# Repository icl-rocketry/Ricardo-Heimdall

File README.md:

Need to add v monitoring to include the buck stuff from chad
Need to add 6v led to know when servo voltage is on

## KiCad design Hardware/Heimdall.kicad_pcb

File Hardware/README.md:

# Ricardo Board Template
This is a KiCad template including the required components for an ESP32S3 with a USB-C port, a CAN transceiver, as well as logic power input regulation. This is the bare minimum needed for boards in the ricardo ecosystem. If you have followed the [hardware library usage instructions](https://github.com/icl-rocketry/iclr-hw), the hardware libraries will automatically be added to every project started from this template.

## Usage
To use this, clone this repository in your KiCad user templates folder.

By default, this folder is:

MacOS - ```/Users/{USERNAME}/Documents/KiCad/8.0/template/```

Windows -  ```%USERPROFILE%/Documents/KiCad/8.0/template```

Linux - ```/home/{USERNAME}/.local/share/kicad/8.0/template```

Then, you will be able to access the template when making a new project in ```KiCad -> File -> New Project from Template... -> User Templates```

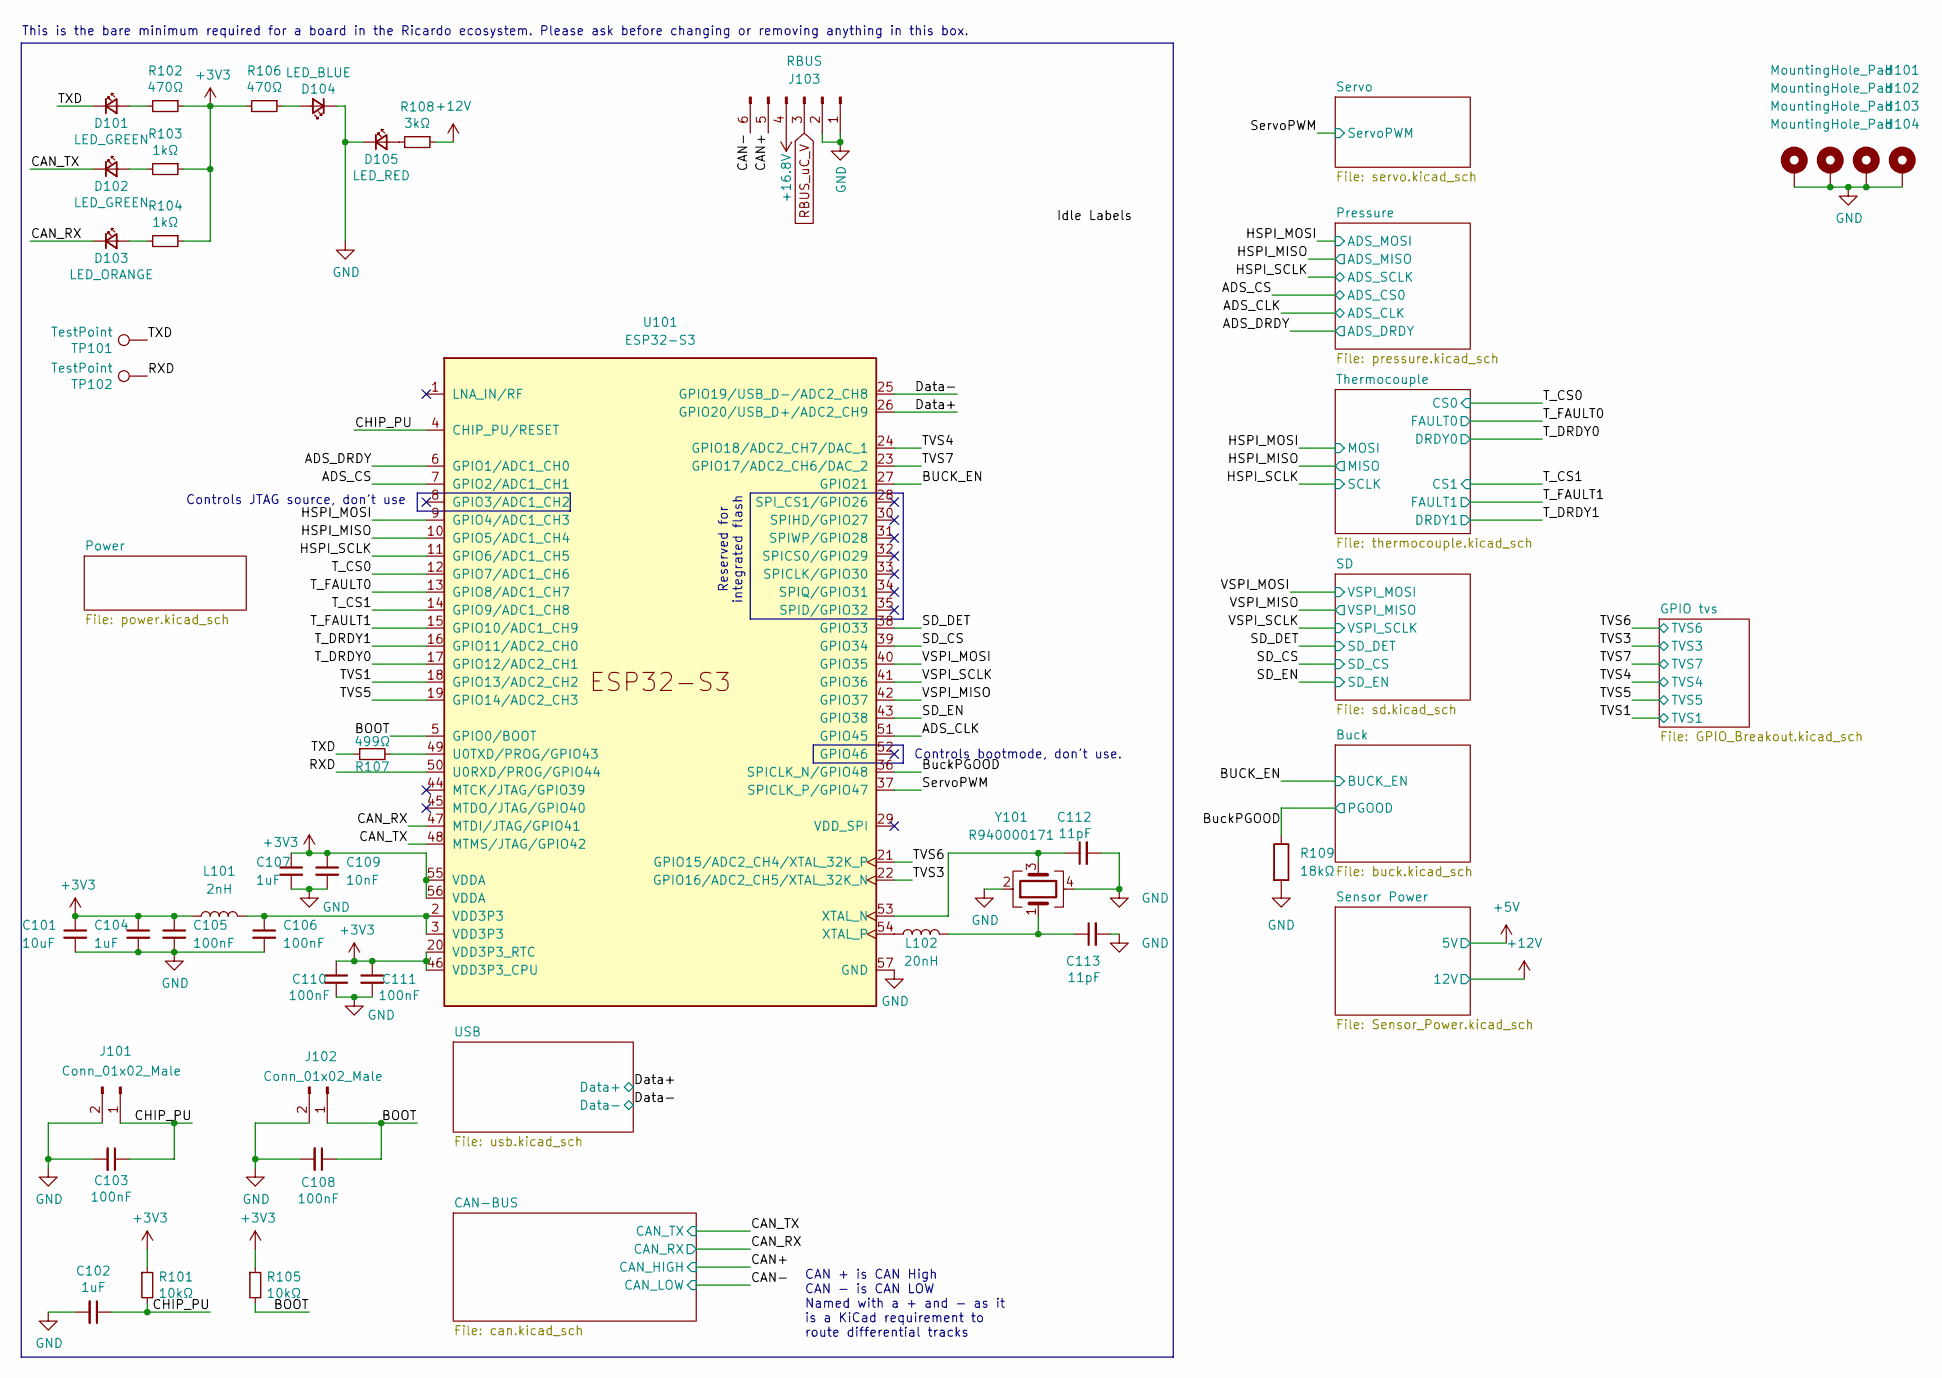
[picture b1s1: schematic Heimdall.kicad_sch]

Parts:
C101: 10uF; C_0402_1005Metric
C102, C104, C107: 1uF; C_0402_1005Metric
C103, C105, C106, C108, C110, C111: 100nF; C_0402_1005Metric
C109: 10nF; C_0402_1005Metric
C112, C113: 11pF; C_0402_1005Metric
D101, D102: LED_GREEN; LED_0402_1005Metric
D103: LED_ORANGE; LED_0402_1005Metric
D104: LED_BLUE; LED_0402_1005Metric
D105: LED_RED; LED_0402_1005Metric
H101, H102, H103, H104: MountingHole_Pad; MountingHole_3.2mm_M3_DIN965_Pad
J101, J102: Conn_01x02_Male; PinHeader_1x02_P2.54mm_Vertical
J103: RBUS; Molex_Mini-Fit_Jr_5569-06A2_2x03_P4.20mm_Horizontal
L101: 2nH; L_0402_1005Metric
L102: 20nH; L_0402_1005Metric
R101, R105: 10kΩ; R_0402_1005Metric
R102, R106: 470Ω; R_0402_1005Metric
R103, R104: 1kΩ; R_0402_1005Metric
R107: 499Ω; R_0402_1005Metric
R108: 3kΩ; R_0402_1005Metric
R109: 18kΩ; R_0402_1005Metric
TP101, TP102: TestPoint; TestPoint_Pad_D1.0mm
U101: ESP32-S3; QFN40P700X700X90-57N
Y101: R940000171; Crystal_SMD_2016-4Pin_2.0x1.6mm

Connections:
+3V3: C101.1, C104.1, C105.1, C107.1, C109.1, C110.1, C111.1, L101.1, R101.1, R102.1, R103.1, R104.1, R105.1, R106.2, U101.20 (VDD3P3_RTC), U101.46 (VDD3P3_CPU), U101.55 (VDDA), U101.56 (VDDA); also elsewhere on the board
+12V: R108.1; also elsewhere on the board
+16.8V: J103.4; also elsewhere on the board
/ADS_CLK: U101.51 (GPIO45); also elsewhere on the board
/ADS_CS: U101.7 (GPIO2/ADC1_CH1); also elsewhere on the board
/ADS_DRDY: U101.6 (GPIO1/ADC1_CH0); also elsewhere on the board
/BOOT: C108.1, J102.1, R105.2, U101.5 (GPIO0/BOOT)
/BUCK_EN: U101.27 (GPIO21); also elsewhere on the board
/BuckPGOOD: R109.1, U101.36 (SPICLK_N/GPIO48); also elsewhere on the board
/CAN+: J103.5; also elsewhere on the board
/CAN-: J103.6; also elsewhere on the board
/CAN_RX: D103.1 (K), U101.47 (MTDI/JTAG/GPIO41); also elsewhere on the board
/CAN_TX: D102.1 (K), U101.48 (MTMS/JTAG/GPIO42); also elsewhere on the board
/CHIP_PU: C102.1, C103.1, J101.1, R101.2, U101.4 (CHIP_PU/RESET)
/Data+: U101.26 (GPIO20/USB_D+/ADC2_CH9); also elsewhere on the board
/Data-: U101.25 (GPIO19/USB_D-/ADC2_CH8); also elsewhere on the board
/HSPI_MISO: U101.10 (GPIO5/ADC1_CH4); also elsewhere on the board
/HSPI_MOSI: U101.9 (GPIO4/ADC1_CH3); also elsewhere on the board
/HSPI_SCLK: U101.11 (GPIO6/ADC1_CH5); also elsewhere on the board
/RXD: TP102.1, U101.50 (U0RXD/PROG/GPIO44)
/SD_CS: U101.39 (GPIO34); also elsewhere on the board
/SD_DET: U101.38 (GPIO33); also elsewhere on the board
/SD_EN: U101.43 (GPIO38); also elsewhere on the board
/ServoPWM: U101.37 (SPICLK_P/GPIO47); also elsewhere on the board
/TVS1: U101.18 (GPIO13/ADC2_CH2); also elsewhere on the board
/TVS3: U101.22 (GPIO16/ADC2_CH5/XTAL_32K_N); also elsewhere on the board
/TVS4: U101.24 (GPIO18/ADC2_CH7/DAC_1); also elsewhere on the board
/TVS5: U101.19 (GPIO14/ADC2_CH3); also elsewhere on the board
/TVS6: U101.21 (GPIO15/ADC2_CH4/XTAL_32K_P); also elsewhere on the board
/TVS7: U101.23 (GPIO17/ADC2_CH6/DAC_2); also elsewhere on the board
/TXD: D101.1 (K), R107.1, TP101.1
/T_CS0: U101.12 (GPIO7/ADC1_CH6); also elsewhere on the board
/T_CS1: U101.14 (GPIO9/ADC1_CH8); also elsewhere on the board
/T_DRDY0: U101.17 (GPIO12/ADC2_CH1); also elsewhere on the board
/T_DRDY1: U101.16 (GPIO11/ADC2_CH0); also elsewhere on the board
/T_FAULT0: U101.13 (GPIO8/ADC1_CH7); also elsewhere on the board
/T_FAULT1: U101.15 (GPIO10/ADC1_CH9); also elsewhere on the board
/VSPI_MISO: U101.42 (GPIO37); also elsewhere on the board
/VSPI_MOSI: U101.40 (GPIO35); also elsewhere on the board
/VSPI_SCLK: U101.41 (GPIO36); also elsewhere on the board
GND: C101.2, C102.2, C103.2, C104.2, C105.2, C106.2, C107.2, C108.2, C109.2, C110.2, C111.2, C112.2, C113.2, D104.1 (K), D105.1 (K), H101.1, H102.1, H103.1, H104.1, J101.2, J102.2, J103.1, J103.2, R109.2, U101.57 (GND), Y101.2, Y101.4; also elsewhere on the board
unnamed: C106.1, L101.2, U101.2 (VDD3P3), U101.3 (VDD3P3)
unnamed: C113.1, L102.2, Y101.1
unnamed: D101.2 (A), R102.2
unnamed: D102.2 (A), R103.2
unnamed: D103.2 (A), R104.2
unnamed: D104.2 (A), R106.1
unnamed: D105.2 (A), R108.2
unnamed: R107.2, U101.49 (U0TXD/PROG/GPIO43)
unnamed: C112.1, U101.53 (XTAL_N), Y101.3
unnamed: L102.1, U101.54 (XTAL_P)
RBUS_uC_V: J103.3; also elsewhere on the board

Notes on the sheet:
Controls bootmode, don't use.
This is the bare minimum required for a board in the Ricardo ecosystem. Please ask before changing or removing anything in this box.
CAN + is CAN High CAN - is CAN LOW Named with a + and - as it is a KiCad requirement to route differential tracks
Controls JTAG source, don't use
Reserved for integrated flash

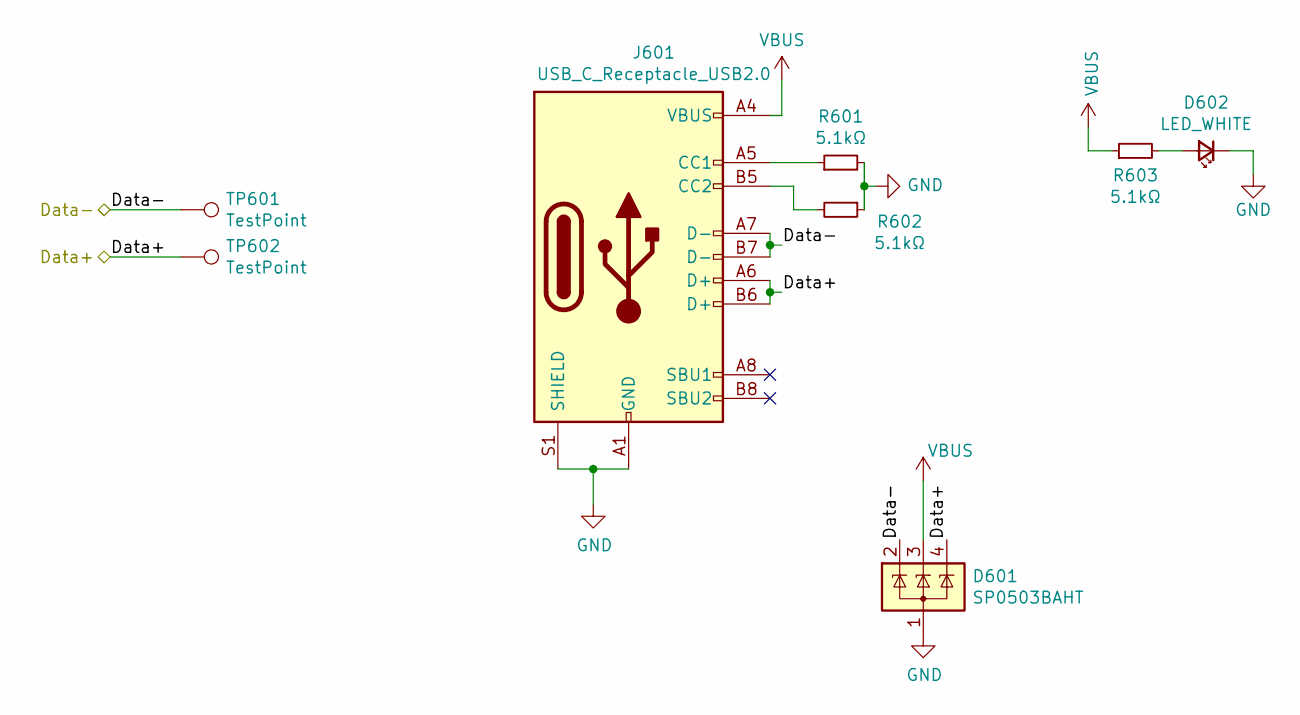
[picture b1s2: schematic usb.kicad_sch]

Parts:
D601: SP0503BAHT; SOT-143
D602: LED_WHITE; LED_0402_1005Metric
J601: USB_C_Receptacle_USB2.0; USB_C_Receptacle_Palconn_UTC16-G
R601, R602, R603: 5.1kΩ; R_0402_1005Metric
TP601, TP602: TestPoint; TestPoint_Pad_D1.0mm

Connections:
/Data+: D601.4 (K), J601.A6 (D+), J601.B6 (D+), TP602.1; also elsewhere on the board
/Data-: D601.2 (K), J601.A7 (D-), J601.B7 (D-), TP601.1; also elsewhere on the board
GND: D601.1 (A), D602.1 (K), J601.A1 (GND), J601.A12 (GND), J601.B1 (GND), J601.B12 (GND), J601.S1 (SHIELD), R601.2, R602.1; also elsewhere on the board
unnamed: D602.2 (A), R603.2
unnamed: J601.A5 (CC1), R601.1
unnamed: J601.B5 (CC2), R602.2
VBUS: D601.3 (K), J601.A4 (VBUS), J601.A9 (VBUS), J601.B4 (VBUS), J601.B9 (VBUS), R603.1; also elsewhere on the board

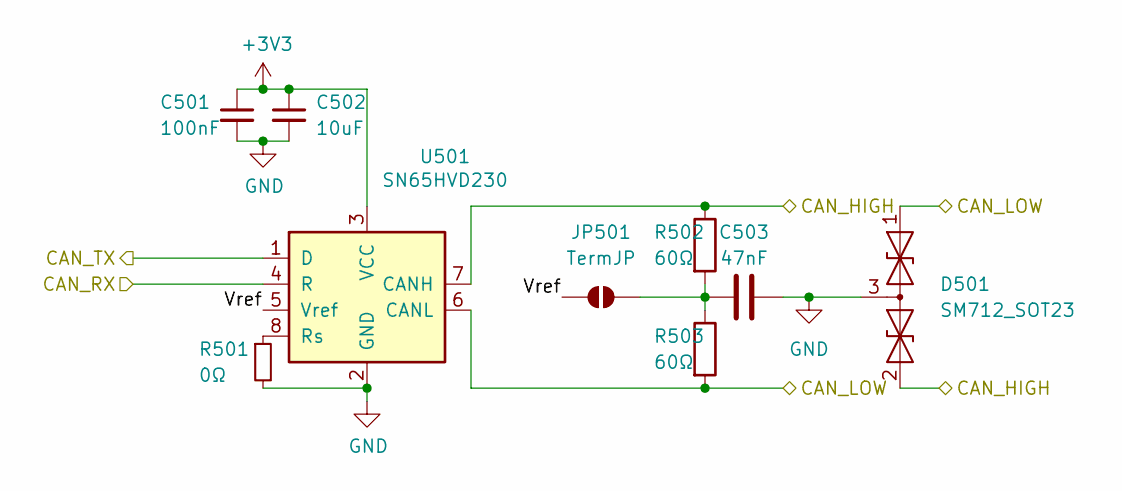
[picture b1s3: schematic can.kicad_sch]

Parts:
C501: 100nF; C_0402_1005Metric
C502: 10uF; C_0402_1005Metric
C503: 47nF; C_0402_1005Metric
D501: SM712_SOT23; SOT-23
JP501: TermJP; SmallerSolderJP
R501: 0Ω; R_0402_1005Metric
R502, R503: 60Ω; R_0603_1608Metric
U501: SN65HVD230; SOIC-8_3.9x4.9mm_P1.27mm

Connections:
+3V3: C501.1, C502.1, U501.3 (VCC); also elsewhere on the board
/CAN+: D501.2 (A2), R502.1, U501.7 (CANH); also elsewhere on the board
/CAN-: D501.1 (A1), R503.2, U501.6 (CANL); also elsewhere on the board
/CAN-BUS/Vref: JP501.1 (A), U501.5 (Vref)
/CAN_RX: U501.4 (R); also elsewhere on the board
/CAN_TX: U501.1 (D); also elsewhere on the board
GND: C501.2, C502.2, C503.2, D501.3 (common), R501.2, U501.2 (GND); also elsewhere on the board
unnamed: C503.1, JP501.2 (B), R502.2, R503.1
unnamed: R501.1, U501.8 (Rs)

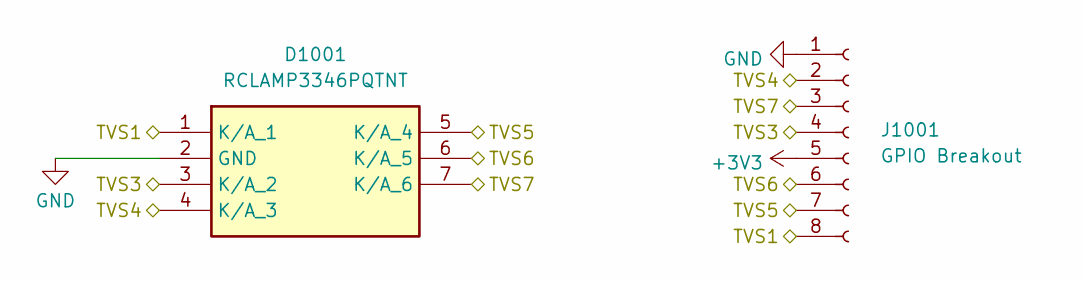
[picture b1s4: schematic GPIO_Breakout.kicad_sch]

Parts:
D1001: RCLAMP3346PQTNT; Mouser Part Number 947-RCLAMP3346PQTNT
J1001: GPIO Breakout; PinSocket_2x04_P2.54mm_Vertical

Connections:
+3V3: J1001.5; also elsewhere on the board
/TVS1: D1001.1 (K/A_1), J1001.8; also elsewhere on the board
/TVS3: D1001.3 (K/A_2), J1001.4; also elsewhere on the board
/TVS4: D1001.4 (K/A_3), J1001.2; also elsewhere on the board
/TVS5: D1001.5 (K/A_4), J1001.7; also elsewhere on the board
/TVS6: D1001.6 (K/A_5), J1001.6; also elsewhere on the board
/TVS7: D1001.7 (K/A_6), J1001.3; also elsewhere on the board
GND: D1001.2 (GND), J1001.1; also elsewhere on the board

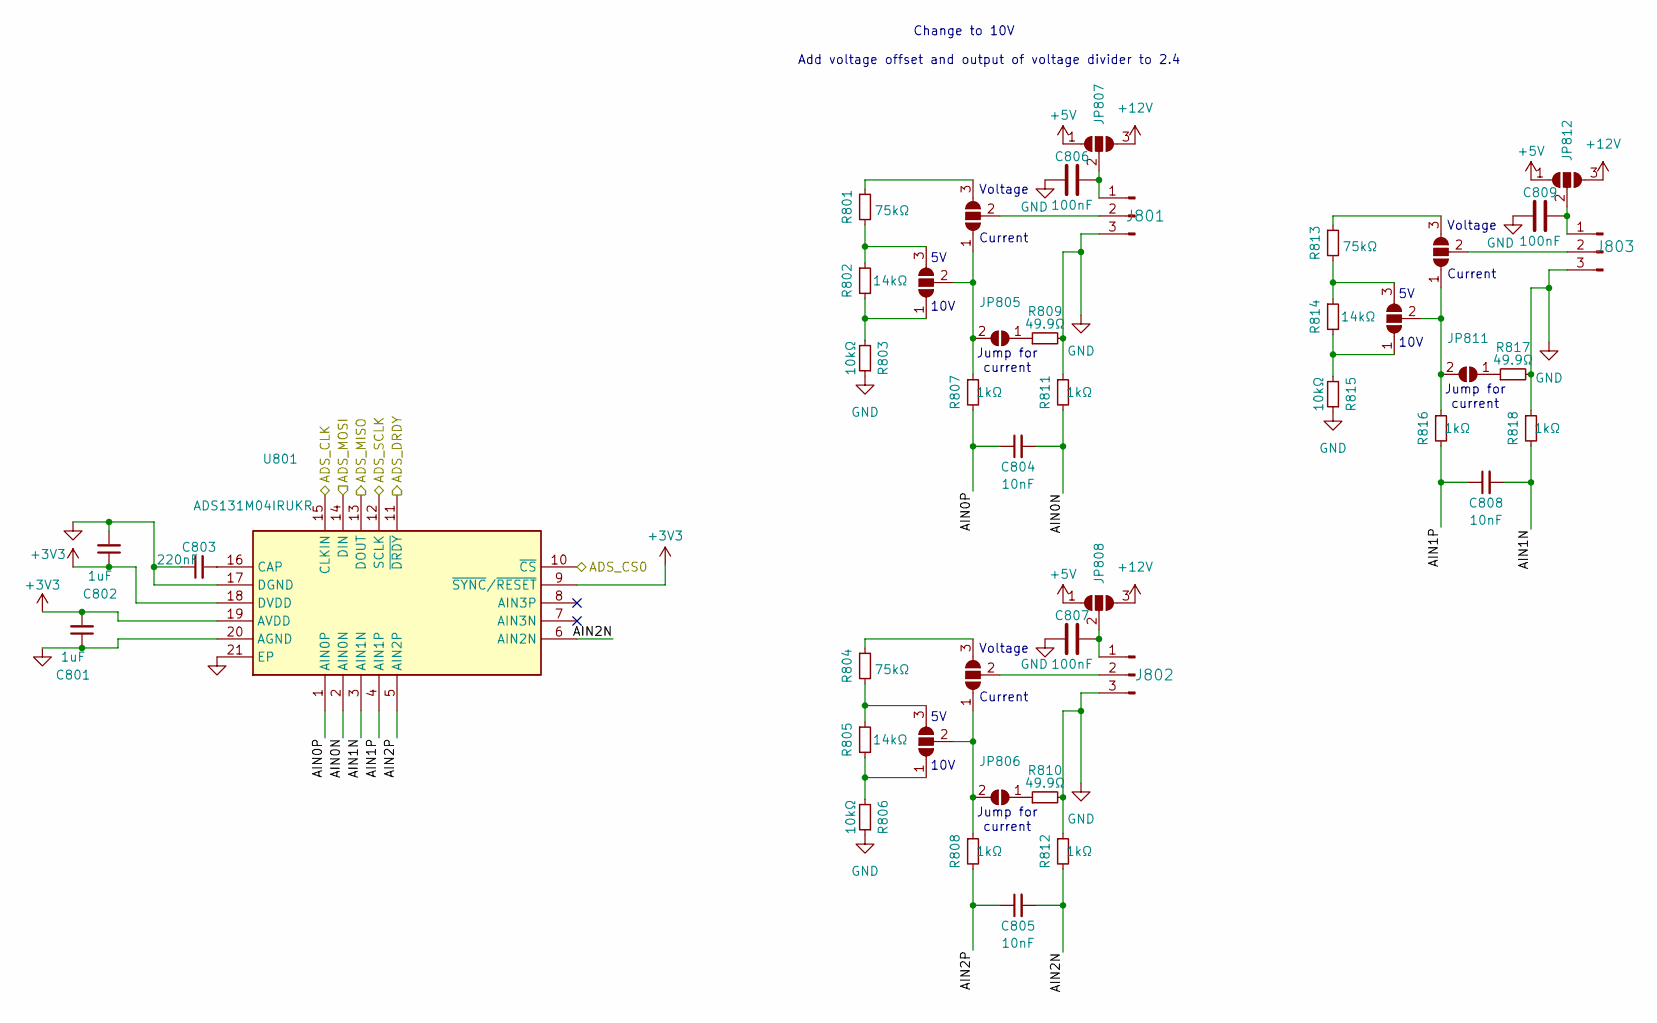
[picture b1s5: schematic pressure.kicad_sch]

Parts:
C801, C802: 1uF; C_0402_1005Metric
C803: 220nF; C_0402_1005Metric
C804, C805, C808: 10nF; C_0402_1005Metric
C806, C807, C809: 100nF; C_0402_1005Metric
J801, J802, J803: 1053131103; Molex_Nano-Fit_105313-xx03_1x03_P2.50mm_Horizontal
JP801, JP802, JP803, JP804, JP807, JP808, JP809, JP810, JP812: SolderJumper_3_Open; SolderJumper-3_P1.3mm_Open_RoundedPad1.0x1.5mm_NumberLabels
JP805, JP806, JP811: SolderJumper_2_Open; SmallerSolderJP
R801, R804, R813: 75kΩ; R_0402_1005Metric; MPN RT0402BRD0775KL
R802, R805, R814: 14kΩ; R_0402_1005Metric; MPN 0402WGF1402TCE
R803, R806, R815: 10kΩ; R_0402_1005Metric; MPN ERA2ARB103X
R807, R808, R811, R812, R816, R818: 1kΩ; R_0402_1005Metric
R809, R810, R817: 49.9Ω; R_0402_1005Metric; MPN RT0402BRD0749R9L
U801: ADS131M04IRUKR; QFN40P300X300X80-21N-D; Manufacturer_Part_Number ADS131M04IRUKR; Mouser Part Number 595-ADS131M04IRUKR

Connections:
+3V3: C801.2, C802.1, U801.9 (~SYNC/~RESET), U801.18 (DVDD), U801.19 (AVDD); also elsewhere on the board
+5V: JP807.1 (A), JP808.1 (A), JP812.1 (A); also elsewhere on the board
+12V: JP807.3 (B), JP808.3 (B), JP812.3 (B); also elsewhere on the board
/ADS_CLK: U801.15 (CLKIN); also elsewhere on the board
/ADS_CS: U801.10 (~CS); also elsewhere on the board
/ADS_DRDY: U801.11 (~DRDY); also elsewhere on the board
/HSPI_MISO: U801.13 (DOUT); also elsewhere on the board
/HSPI_MOSI: U801.14 (DIN); also elsewhere on the board
/HSPI_SCLK: U801.12 (SCLK); also elsewhere on the board
/Pressure/AIN0N: C804.2, R811.2, U801.2 (AIN0N)
/Pressure/AIN0P: C804.1, R807.2, U801.1 (AIN0P)
/Pressure/AIN1N: C808.2, R818.2, U801.3 (AIN1N)
/Pressure/AIN1P: C808.1, R816.2, U801.4 (AIN1P)
/Pressure/AIN2N: C805.2, R812.2, U801.6 (AIN2N)
/Pressure/AIN2P: C805.1, R808.2, U801.5 (AIN2P)
GND: C801.1, C802.2, C803.1, C806.1, C807.1, C809.1, J801.3, J802.3, J803.3, R803.1, R806.1, R809.2, R810.2, R811.1, R812.1, R815.1, R817.2, R818.1, U801.17 (DGND), U801.20 (AGND), U801.21 (EP); also elsewhere on the board
unnamed: C806.2, J801.1, JP807.2 (C)
unnamed: J801.2, JP803.2 (C)
unnamed: C807.2, J802.1, JP808.2 (C)
unnamed: J802.2, JP804.2 (C)
unnamed: C809.2, J803.1, JP812.2 (C)
unnamed: J803.2, JP810.2 (C)
unnamed: JP801.1 (A), R802.2, R803.2
unnamed: JP801.3 (B), R801.2, R802.1
unnamed: JP801.2 (C), JP803.1 (A), JP805.2 (B), R807.1
unnamed: JP802.1 (A), R805.2, R806.2
unnamed: JP802.3 (B), R804.2, R805.1
unnamed: JP802.2 (C), JP804.1 (A), JP806.2 (B), R808.1
unnamed: JP803.3 (B), R801.1
unnamed: JP804.3 (B), R804.1
unnamed: JP805.1 (A), R809.1
unnamed: JP806.1 (A), R810.1
unnamed: JP809.1 (A), R814.2, R815.2
unnamed: JP809.3 (B), R813.2, R814.1
unnamed: JP809.2 (C), JP810.1 (A), JP811.2 (B), R816.1
unnamed: JP810.3 (B), R813.1
unnamed: JP811.1 (A), R817.1
unnamed: C803.2, U801.16 (CAP)

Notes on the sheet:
Jump for current
10V
Add voltage offset and output of voltage divider to 2.4
Voltage
Change to 10V
Current

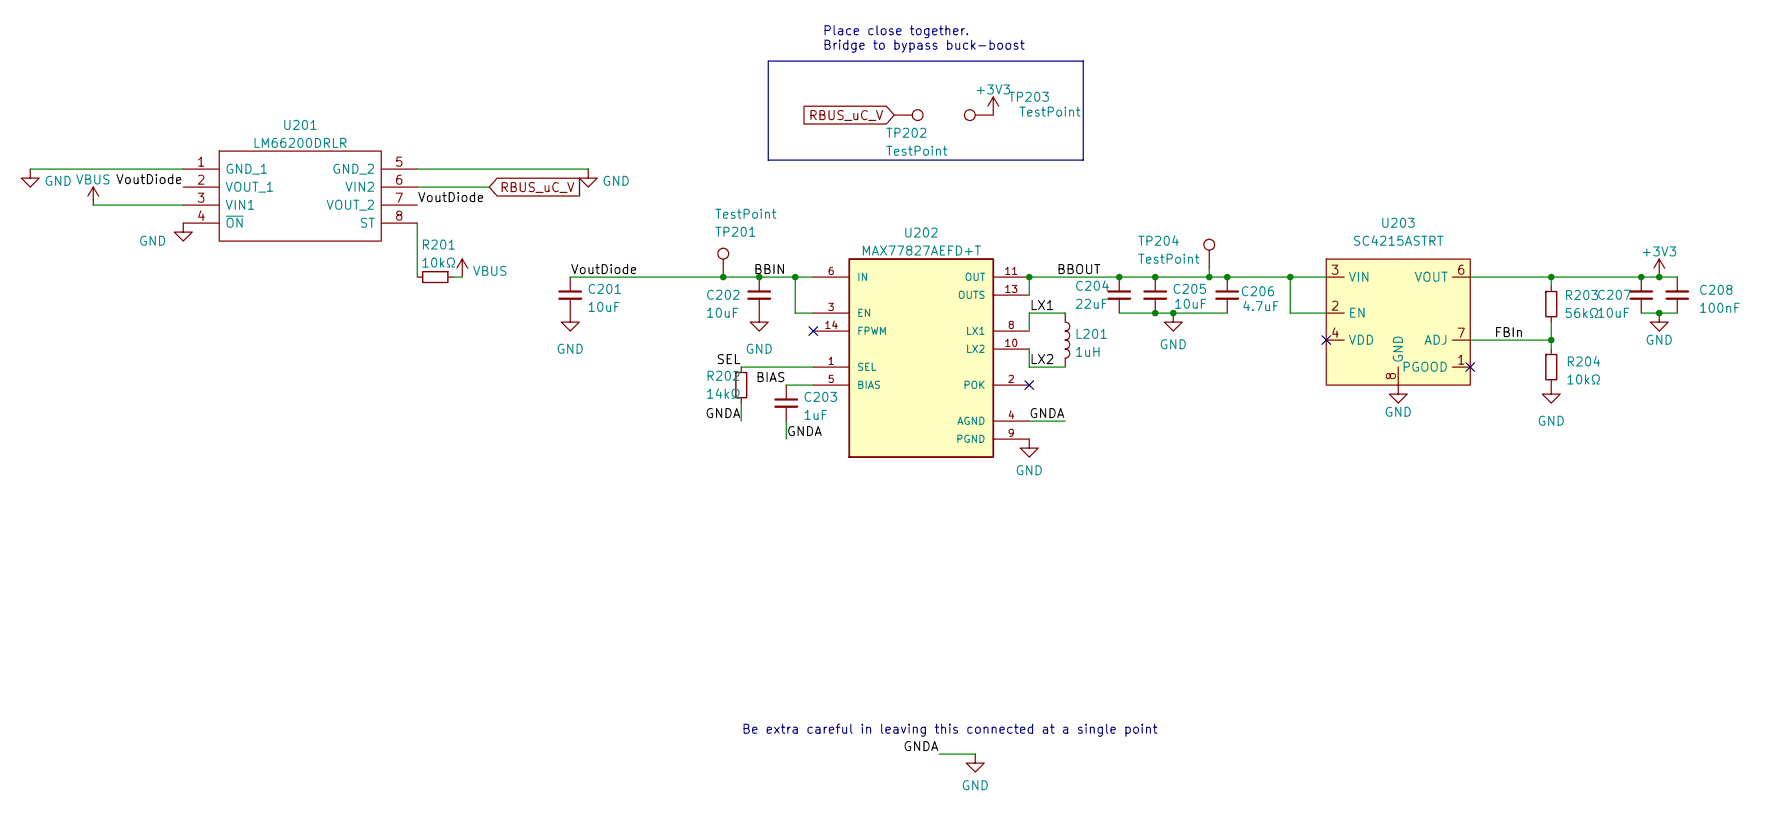
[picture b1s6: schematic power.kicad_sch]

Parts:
C201, C205, C207: 10uF; C_0402_1005Metric
C202: 10uF; C_0603_1608Metric
C203: 1uF; C_0402_1005Metric
C204: 22uF; C_0603_1608Metric
C206: 4.7uF; C_0402_1005Metric
C208: 100nF; C_0402_1005Metric
L201: 1uH; L_0805_2012Metric
R201, R204: 10kΩ; R_0402_1005Metric
R202: 14kΩ; R_0402_1005Metric
R203: 56kΩ; R_0402_1005Metric
TP201, TP202, TP203, TP204: TestPoint; TestPoint_Pad_D1.5mm
U201: LM66200DRLR; SOTFL50P160X60-8N; Manufacturer_Part_Number LM66200DRLR; Mouser Part Number 595-LM66200DRLR
U202: MAX77827AEFD+T; CONV_MAX77827AEFD+T; PARTREV B
U203: SC4215ASTRT; SOIC127P599X175-9N

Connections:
+3V3: C207.2, C208.2, R203.1, TP203.1, U203.6 (VOUT); also elsewhere on the board
/Power/BBIN: C201.1, C202.1, TP201.1, U201.2 (VOUT_1), U201.7 (VOUT_2), U202.3 (EN), U202.6 (IN)
/Power/BBOUT: C204.1, C205.1, C206.1, TP204.1, U202.11 (OUT), U202.13 (OUTS), U203.2 (EN), U203.3 (VIN)
/Power/BIAS: C203.1, U202.5 (BIAS)
/Power/FBIn: R203.2, R204.1, U203.7 (ADJ)
/Power/LX1: L201.1, U202.8 (LX1)
/Power/LX2: L201.2, U202.10 (LX2)
/Power/SEL: R202.1, U202.1 (SEL)
GND: C201.2, C202.2, C203.2, C204.2, C205.2, C206.2, C207.1, C208.1, R202.2, R204.2, U201.1 (GND_1), U201.4 (~ON), U201.5 (GND_2), U202.4 (AGND), U202.9 (PGND), U203.8 (GND), U203.9 (GND); also elsewhere on the board
unnamed: R201.2, U201.8 (ST)
RBUS_uC_V: TP202.1, U201.6 (VIN2); also elsewhere on the board
VBUS: R201.1, U201.3 (VIN1); also elsewhere on the board

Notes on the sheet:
Place close together. Bridge to bypass buck-boost
Be extra careful in leaving this connected at a single point

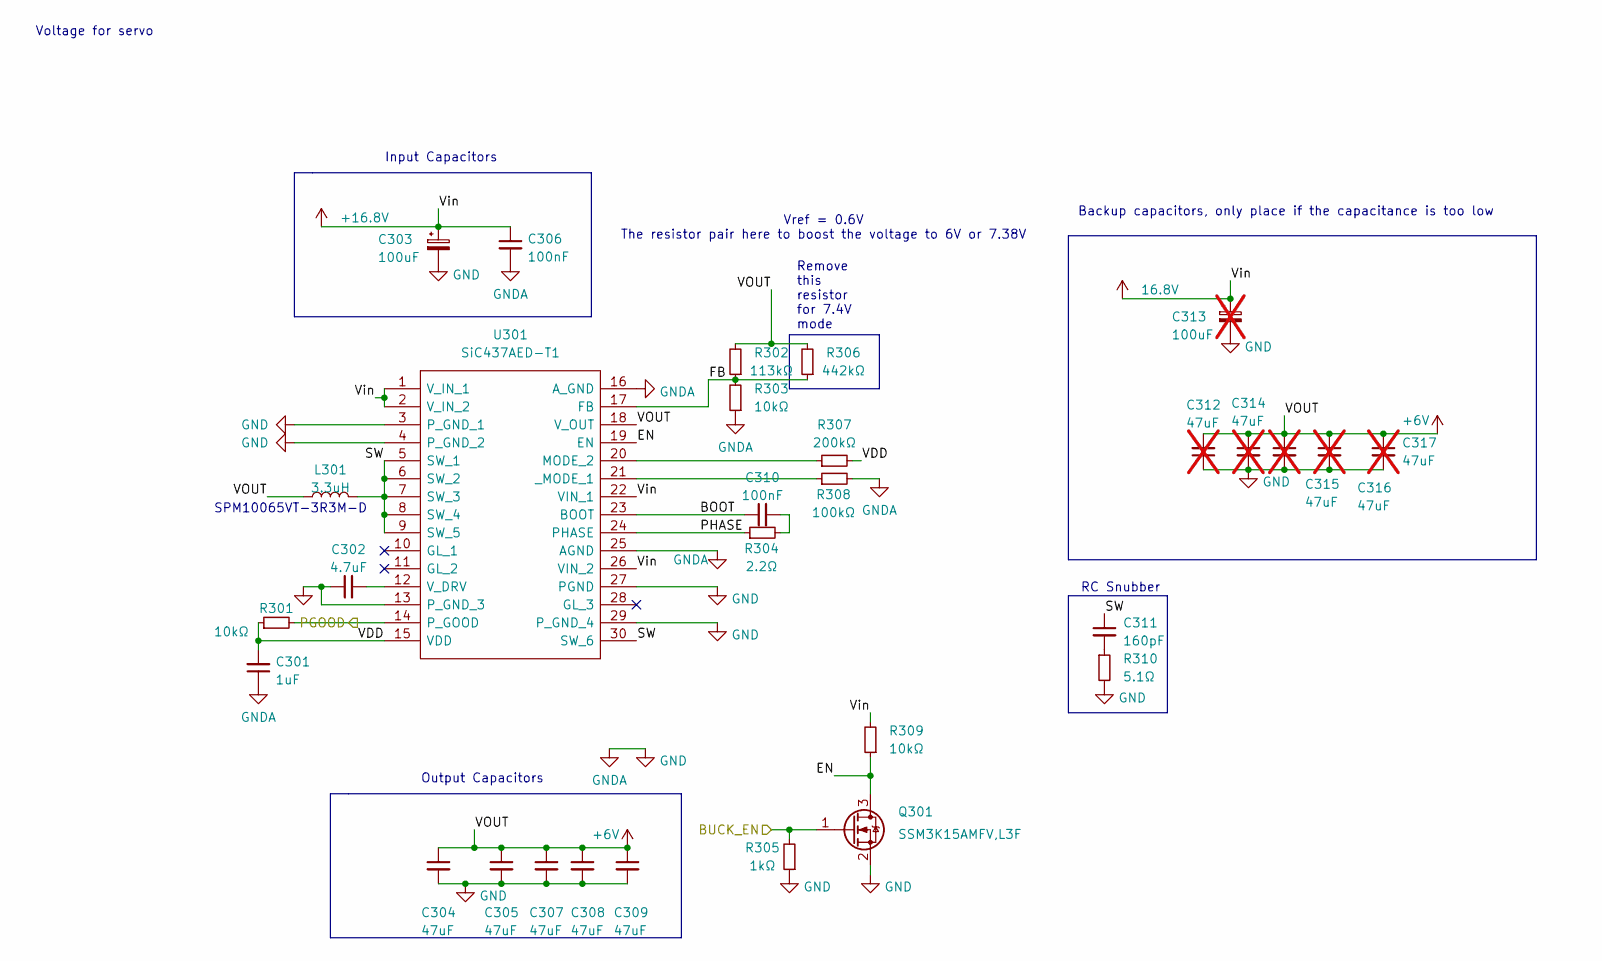
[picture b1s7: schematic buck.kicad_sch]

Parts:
C301: 1uF; C_0402_1005Metric
C302: 4.7uF; C_0402_1005Metric
C303: 100uF; CP_EIA-7360-38_Kemet-E; MPN T52M1107M035C0100
C304, C305, C307, C308, C309: 47uF; C_1206_3216Metric
C306, C310: 100nF; C_0402_1005Metric
C311: 160pF; C_0603_1608Metric
C312, C314, C315, C316, C317: 47uF; C_1206_3216Metric; not fitted
C313: 100uF; CP_EIA-7360-38_Kemet-E; MPN T52M1107M035C0100; not fitted
L301: 3.3uH; IND_SPM10065VT-3R3M-D; MPN SPM10065VT-3R3M-D
Q301: SSM3K15AMFV,L3F; SOT-723
R301, R303, R309: 10kΩ; R_0402_1005Metric
R302: 113kΩ; R_0402_1005Metric; MPN ERJ-2RKF1133X
R304: 2.2Ω; R_0402_1005Metric
R305: 1kΩ; R_0402_1005Metric
R306: 442kΩ; R_0402_1005Metric; MPN ERJ-2RKF4423X
R307: 200kΩ; R_0402_1005Metric
R308: 100kΩ; R_0402_1005Metric
R310: 5.1Ω; R_0603_1608Metric
U301: SiC437AED-T1; SiC437BEDT1GE3; Manufacturer_Part_Number SiC437BED-T1-GE3; Mouser Part Number 78-SIC437BED-T1-GE3

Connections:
+6V: C304.1, C305.1, C307.1, C308.1, C309.1, C312.2, C314.1, C315.1, C316.1, C317.1, L301.1, R302.2, R306.2, U301.18 (V_OUT); also elsewhere on the board
+16.8V: C303.1, C306.1, C313.1, R309.2, U301.1 (V_IN_1), U301.2 (V_IN_2), U301.22 (VIN_1), U301.26 (VIN_2); also elsewhere on the board
/BUCK_EN: Q301.1 (G), R305.2; also elsewhere on the board
/Buck/BOOT: C310.1, U301.23 (BOOT)
/Buck/EN: Q301.3 (D), R309.1, U301.19 (EN)
/Buck/FB: R302.1, R303.2, R306.1, U301.17 (FB)
/Buck/PHASE: R304.1, U301.24 (PHASE)
/Buck/SW: C311.1, L301.2, U301.5 (SW_1), U301.6 (SW_2), U301.7 (SW_3), U301.8 (SW_4), U301.9 (SW_5), U301.30 (SW_6)
/Buck/VDD: C301.2, R301.1, R307.2, U301.15 (VDD)
/BuckPGOOD: R301.2, U301.14 (P_GOOD); also elsewhere on the board
GND: C301.1, C302.1, C303.2, C304.2, C305.2, C306.2, C307.2, C308.2, C309.2, C312.1, C313.2, C314.2, C315.2, C316.2, C317.2, Q301.2 (S), R303.1, R305.1, R308.2, R310.2, U301.3 (P_GND_1), U301.4 (P_GND_2), U301.13 (P_GND_3), U301.16 (A_GND), U301.25 (AGND), U301.27 (PGND), U301.29 (P_GND_4); also elsewhere on the board
unnamed: C310.2, R304.2
unnamed: C311.2, R310.1
unnamed: R307.1, U301.20 (MODE_2)
unnamed: C302.2, U301.12 (V_DRV)
unnamed: R308.1, U301.21 (_MODE_1)

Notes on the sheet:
SPM10065VT-3R3M-D
Voltage for servo
Output Capacitors
Backup capacitors, only place if the capacitance is too low
Input Capacitors
Vref = 0.6V The resistor pair here to boost the voltage to 6V or 7.38V
RC Snubber
Remove this resistor for 7.4V mode

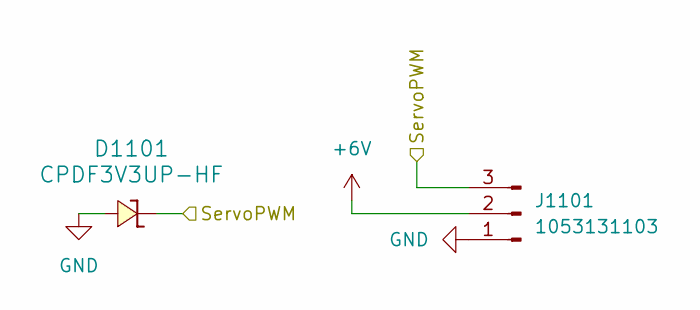
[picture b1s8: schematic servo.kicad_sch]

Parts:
D1101: CPDF3V3UP-HF; CPD
J1101: 1053131103; Molex_Nano-Fit_105313-xx03_1x03_P2.50mm_Horizontal

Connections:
+6V: J1101.2; also elsewhere on the board
/ServoPWM: D1101.2, J1101.3; also elsewhere on the board
GND: D1101.1, J1101.1; also elsewhere on the board

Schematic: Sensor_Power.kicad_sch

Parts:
C401: 2.2uF; C_0603_1608Metric
C402: 180pF; C_0402_1005Metric
C403: 3.9nF; C_0402_1005Metric
C404, C413: 1uF; C_0402_1005Metric; MPN CL05X105KA5NQNC
C405, C406, C417, C419: 22uF; C_0805_2012Metric
C407, C409, C420, C421: 100nF; C_0402_1005Metric
C408, C418: 2.2uF; C_0402_1005Metric; MPN GRM155R61E225ME15D
C410: 47uF; C_1206_3216Metric
C411, C422: 10uF; C_0603_1608Metric; MPN TMK107BBJ106MA-T
C412, C423: 100nF; C_0402_1005Metric; MPN C1005X5R1E104KT000E
C414: 10uF; C_0603_1608Metric
C415: 120pF; C_0402_1005Metric
C416: 2.2nF; C_0402_1005Metric
C424: 22uF; C_1206_3216Metric
D401: CPDF5V0U-HF; CPD
L401, L402: 5uH; IND_SRP6540-390M; Manufacturer_Part_Number SRR6038-5R0Y; Mouser Part Number 652-SRR6038-5R0Y
R401: 7.87kΩ; R_0402_1005Metric
R402: 360kΩ; R_0402_1005Metric
R403, R411: 100kΩ; R_0402_1005Metric
R404, R414: 10kΩ; R_0402_1005Metric
R405: 560kΩ; R_0402_1005Metric
R406, R412: 49.9kΩ; R_0402_1005Metric
R407: 150kΩ; R_0603_1608Metric
R408: 301kΩ; R_0402_1005Metric
R409: 18.7kΩ; R_0402_1005Metric
R410: 976kΩ; R_0402_1005Metric
R413: 432kΩ; R_0402_1005Metric
R415: 475kΩ; R_0402_1005Metric
R416: 287kΩ; R_0402_1005Metric
U401, U404: TPS61089RNRR; IC_TPS61089RNRR; Manufacturer_Part_Number TPS61089RNRR; Mouser Part Number 595-TPS61089RNRR
U402, U403: AP2205-W5-7; SOT95P282X145-5N; Mouser Part Number 621-AP2205-W5-7

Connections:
+3V3: C409.1, C410.1, C421.1, C424.1, L401.1, L402.1, R404.2, R414.2, U401.9 (VIN), U404.9 (VIN); also elsewhere on the board
+5V: C408.1, D401.2, R407.2, U402.5 (VOUT); also elsewhere on the board
+12V: C418.1, R413.2, U403.5 (VOUT); also elsewhere on the board
/Sensor Power/FB_5V: R402.1, R403.2, U401.3 (FB)
/Sensor Power/FB_12V: R410.1, R411.2, U404.3 (FB)
/Sensor Power/LDO5.5V_IN: C404.1, C405.1, C406.1, C411.1, C412.1, R402.2, U401.6 (VOUT), U402.1 (VIN), U402.3 (EN)
/Sensor Power/LDO12V_IN: C413.1, C417.1, C419.1, C422.1, C423.1, R410.2, U403.1 (VIN), U403.3 (EN), U404.6 (VOUT)
/Sensor Power/SW_5V: R408.1, U401.1 (FSW)
/Sensor Power/SW_12V: R416.1, U404.1 (FSW)
GND: C401.2, C402.2, C403.2, C404.2, C405.2, C406.2, C408.2, C409.2, C410.2, C411.2, C412.2, C413.2, C414.2, C415.2, C416.2, C417.2, C418.2, C419.2, C421.2, C422.2, C423.2, C424.2, D401.1, R403.1, R405.1, R406.1, R411.1, R412.1, R415.1, U401.5 (GND), U402.2 (GND), U403.2 (GND), U404.5 (GND); also elsewhere on the board
unnamed: C403.1, R401.2
unnamed: C416.1, R409.2
unnamed: C407.1, U401.10 (BOOT)
unnamed: C402.1, R401.1, U401.4 (COMP)
unnamed: R404.1, U401.7 (EN)
unnamed: R405.2, U401.8 (ILIM)
unnamed: C407.2, L401.2, R408.2, U401.11 (SW)
unnamed: C401.1, U401.2 (VCC)
unnamed: R406.2, R407.1, U402.4 (ADJ/NC)
unnamed: R412.2, R413.1, U403.4 (ADJ/NC)
unnamed: C420.1, U404.10 (BOOT)
unnamed: C415.1, R409.1, U404.4 (COMP)
unnamed: R414.1, U404.7 (EN)
unnamed: R415.2, U404.8 (ILIM)
unnamed: C420.2, L402.2, R416.2, U404.11 (SW)
unnamed: C414.1, U404.2 (VCC)

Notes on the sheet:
SIM: https://webench.ti.com/appinfo/webench/scripts/SDP.cgi?ID=0086ECB0F8B2BBA7
SIM: https://webench.ti.com/appinfo/webench/scripts/SDP.cgi?ID=C25BB1AA15C31C1A

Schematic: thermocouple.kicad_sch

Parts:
C901, C903, C906, C908: 10nF; C_0402_1005Metric
C902, C904, C905, C907, C909, C910: 100nF; C_0402_1005Metric
J901, J902: 1053131102; Molex_Nano-Fit_105313-xx02_1x02_P2.50mm_Horizontal
R901, R902, R903, R904: 100Ω; R_0402_1005Metric
U901, U902: MAX31856; TSSOP-14_4.4x5mm_P0.65mm

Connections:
+3V3: C904.2, C905.2, C909.2, C910.2, U901.5 (AVDD), U901.8 (DVDD), U902.5 (AVDD), U902.8 (DVDD); also elsewhere on the board
/HSPI_MISO: U901.11 (SDO), U902.11 (SDO); also elsewhere on the board
/HSPI_MOSI: U901.12 (SDI), U902.12 (SDI); also elsewhere on the board
/HSPI_SCLK: U901.10 (SCK), U902.10 (SCK); also elsewhere on the board
/T_CS0: U902.9 (~CS); also elsewhere on the board
/T_CS1: U901.9 (~CS); also elsewhere on the board
/T_DRDY0: U902.7 (~DRDY); also elsewhere on the board
/T_DRDY1: U901.7 (~DRDY); also elsewhere on the board
/T_FAULT0: U902.13 (~FAULT); also elsewhere on the board
/T_FAULT1: U901.13 (~FAULT); also elsewhere on the board
GND: C901.1, C903.2, C904.1, C905.1, C906.1, C908.2, C909.1, C910.1, U901.1 (AGND), U901.14 (DGND), U902.1 (AGND), U902.14 (DGND); also elsewhere on the board
unnamed: J901.1 (+), R901.2
unnamed: J901.2 (-), R902.1, U901.2 (BIAS)
unnamed: J902.1 (+), R903.2
unnamed: J902.2 (-), R904.1, U902.2 (BIAS)
unnamed: C901.2, C902.1, R901.1, U901.4 (T+)
unnamed: C902.2, C903.1, R902.2, U901.3 (T-)
unnamed: C906.2, C907.1, R903.1, U902.4 (T+)
unnamed: C907.2, C908.1, R904.2, U902.3 (T-)

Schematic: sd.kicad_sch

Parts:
C701: 100nF; C_0402_1005Metric
J701: ST1W008S4TR2000; JAE_ST1W008S4TR2000; PARTREV 1
JP701: SolderJumper_2_Open; SmallerSolderJP
Q701: DMP3099L; SOT-23; MPN DMP3099L
R701: 1kΩ; R_0402_1005Metric
R702: 10kΩ; R_0402_1005Metric

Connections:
+3V3: JP701.1 (A), Q701.3 (S), R702.2; also elsewhere on the board
/SD_CS: J701.C2; also elsewhere on the board
/SD_DET: J701.SW, R702.1; also elsewhere on the board
/SD_EN: Q701.2 (G), R701.2; also elsewhere on the board
/VSPI_MISO: J701.C7; also elsewhere on the board
/VSPI_MOSI: J701.C3; also elsewhere on the board
/VSPI_SCLK: J701.C5; also elsewhere on the board
GND: C701.2, J701.C6, J701.GND1 (GND), J701.GND2 (GND), J701.GND3 (GND), J701.GND4 (GND), R701.1; also elsewhere on the board
unnamed: C701.1, J701.C4, JP701.2 (B), Q701.1 (D)
